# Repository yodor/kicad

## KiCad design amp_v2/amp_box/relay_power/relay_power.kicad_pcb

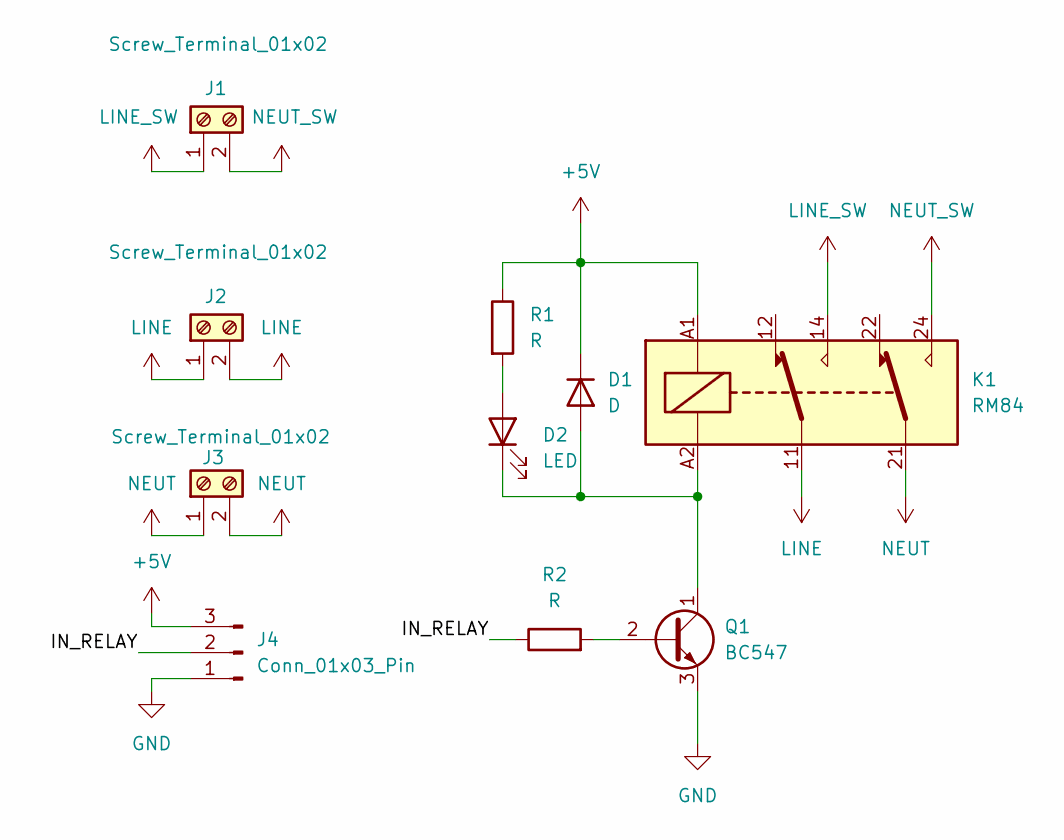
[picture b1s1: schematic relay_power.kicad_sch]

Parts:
D1: D; D_A-405_P7.62mm_Horizontal
D2: LED; LED_Rectangular_W5.0mm_H2.0mm
J1, J2, J3: Screw_Terminal_01x02; TerminalBlock_MaiXu_MX126-5.0-02P_1x02_P5.00mm
J4: Conn_01x03_Pin; PinHeader_1x03_P2.54mm_Vertical
K1: RM84; Relay_DPDT_Finder_40.52
Q1: BC547; TO-92_Inline_Wide
R1, R2: R; R_Axial_DIN0207_L6.3mm_D2.5mm_P10.16mm_Horizontal

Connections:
+5V: D1.1 (K), J4.3, K1.A1, R1.1
/IN_RELAY: J4.2, R2.1
GND: J4.1, Q1.3 (E)
LINE: J2.1, J2.2, K1.11
LINE_SW: J1.1, K1.14
NEUT: J3.1, J3.2, K1.21
NEUT_SW: J1.2, K1.24
unnamed: D1.2 (A), D2.1 (K), K1.A2, Q1.1 (C)
unnamed: D2.2 (A), R1.2
unnamed: Q1.2 (B), R2.2

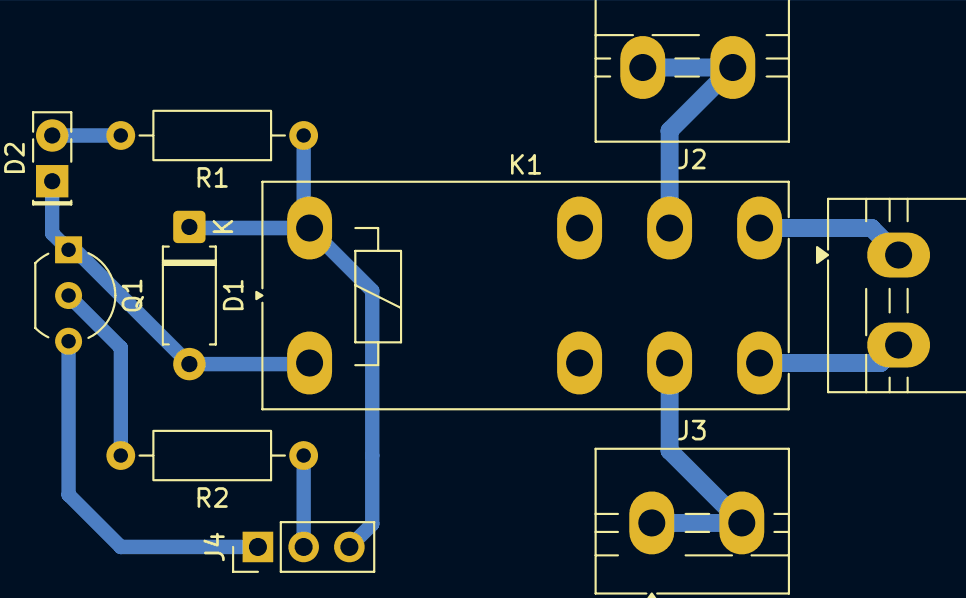
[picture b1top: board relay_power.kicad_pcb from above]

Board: 2 copper layers, 10 parts (0 on the bottom side), 10 nets.

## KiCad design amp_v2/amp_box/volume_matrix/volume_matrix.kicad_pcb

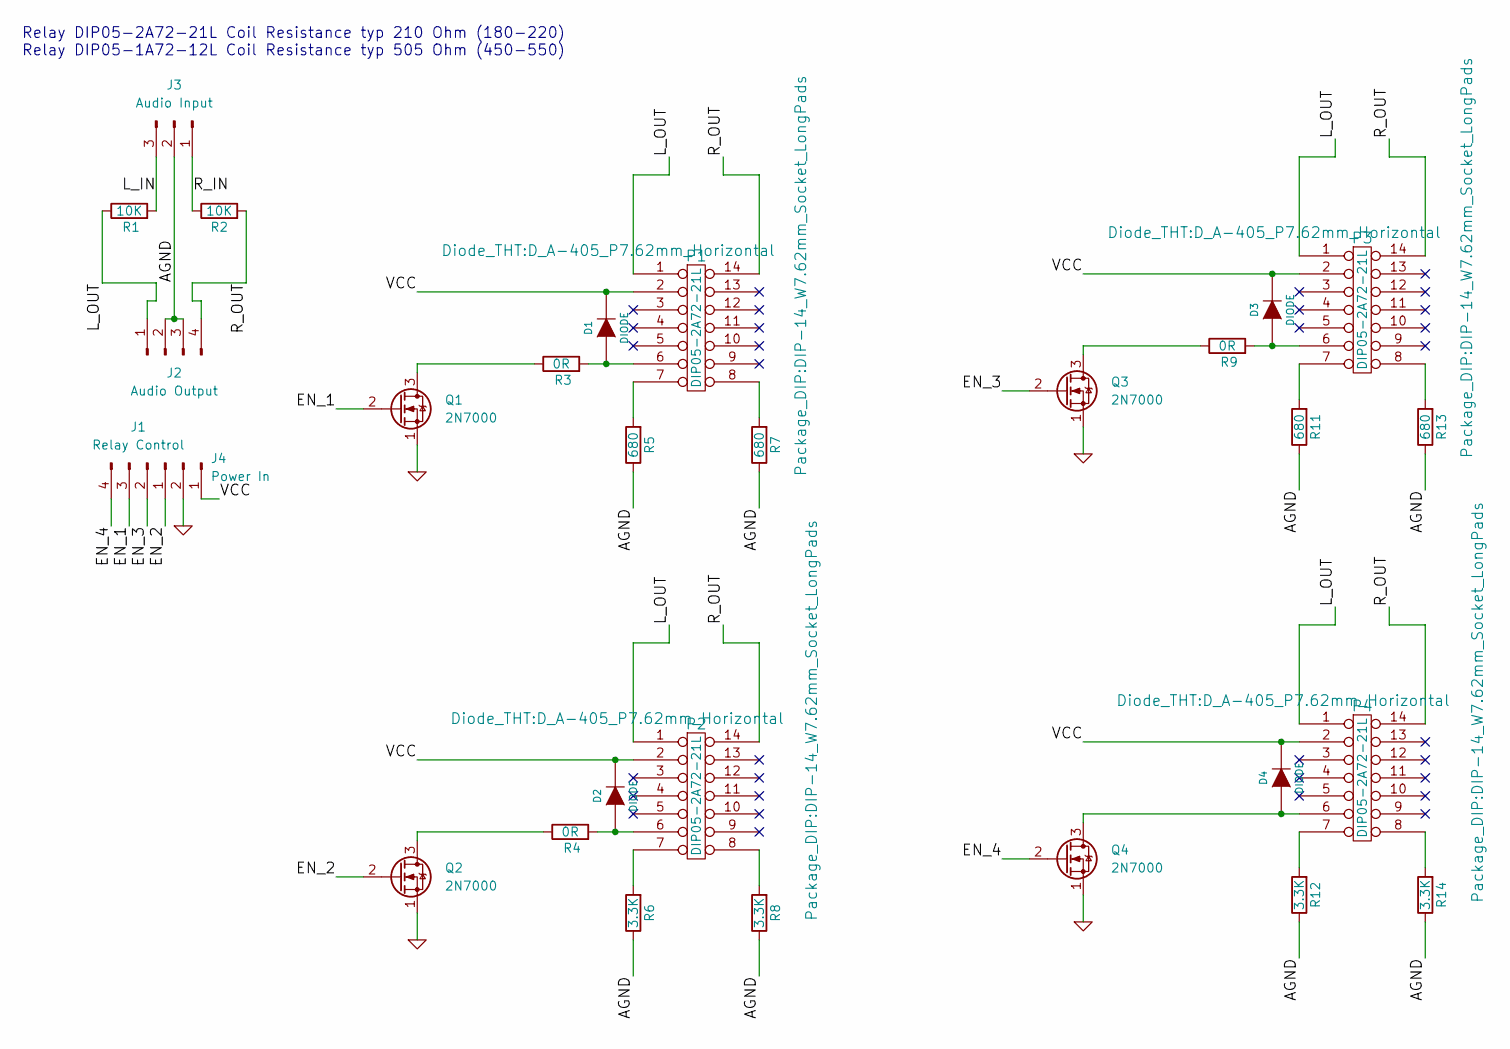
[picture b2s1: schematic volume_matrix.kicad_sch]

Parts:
D1, D2, D3, D4: DIODE; D_A-405_P7.62mm_Horizontal
J1: Relay Control; PinHeader_1x04_P2.54mm_Vertical
J2: Audio Output; JST_XH_B4B-XH-A_1x04_P2.50mm_Vertical
J3: Audio Input; JST_XH_B3B-XH-A_1x03_P2.50mm_Vertical
J4: Power In; PinHeader_1x02_P2.54mm_Vertical
P1, P2, P3, P4: DIP05-2A72-21L; DIP-14_W7.62mm_Socket_LongPads
Q1, Q2, Q3, Q4: 2N7000; TO-92L_Inline_Wide
R1, R2: 10K; R_Axial_DIN0207_L6.3mm_D2.5mm_P7.62mm_Horizontal
R3, R4, R9: 0R; R_Axial_DIN0411_L9.9mm_D3.6mm_P12.70mm_Horizontal
R5, R7, R11, R13: 680; R_Axial_DIN0207_L6.3mm_D2.5mm_P7.62mm_Horizontal
R6, R8, R12, R14: 3.3K; R_Axial_DIN0207_L6.3mm_D2.5mm_P7.62mm_Horizontal

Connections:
/AGND: J2.2, J2.3, J3.2, R5.1, R6.1, R7.1, R8.1, R11.1, R12.1, R13.1, R14.1
/EN_1: J1.3, Q1.2 (G)
/EN_2: J1.1, Q2.2 (G)
/EN_3: J1.2, Q3.2 (G)
/EN_4: J1.4, Q4.2 (G)
/L_IN: J3.3, R1.2
/L_OUT: J2.1, P1.1, P2.1, P3.1, P4.1, R1.1
/R_IN: J3.1, R2.1
/R_OUT: J2.4, P1.14, P2.14, P3.14, P4.14, R2.2
/VCC: D1.2 (K), D2.2 (K), D3.2 (K), D4.2 (K), J4.1, P1.2, P2.2, P3.2, P4.2
GND: J4.2, Q1.1 (S), Q2.1 (S), Q3.1 (S), Q4.1 (S)
unnamed: D1.1 (A), P1.6, R3.2
unnamed: D2.1 (A), P2.6, R4.2
unnamed: D3.1 (A), P3.6, R9.2
unnamed: D4.1 (A), P4.6, Q4.3 (D)
unnamed: P1.7, R5.2
unnamed: P1.8, R7.2
unnamed: P2.7, R6.2
unnamed: P2.8, R8.2
unnamed: P3.7, R11.2
unnamed: P3.8, R13.2
unnamed: P4.7, R12.2
unnamed: P4.8, R14.2
unnamed: Q1.3 (D), R3.1
unnamed: Q2.3 (D), R4.1
unnamed: Q3.3 (D), R9.1

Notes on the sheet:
Relay DIP05-2A72-21L Coil Resistance typ 210 Ohm (180-220) Relay DIP05-1A72-12L Coil Resistance typ 505 Ohm (450-550)

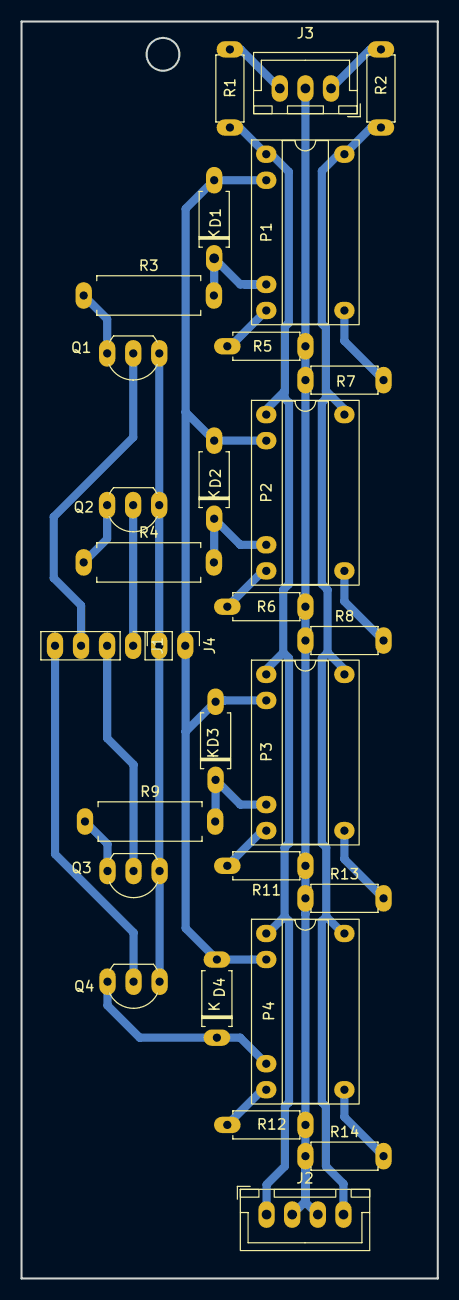
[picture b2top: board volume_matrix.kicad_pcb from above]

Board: 2 copper layers, 40.6 x 122.6 mm, 29 parts (0 on the bottom side), 26 nets.

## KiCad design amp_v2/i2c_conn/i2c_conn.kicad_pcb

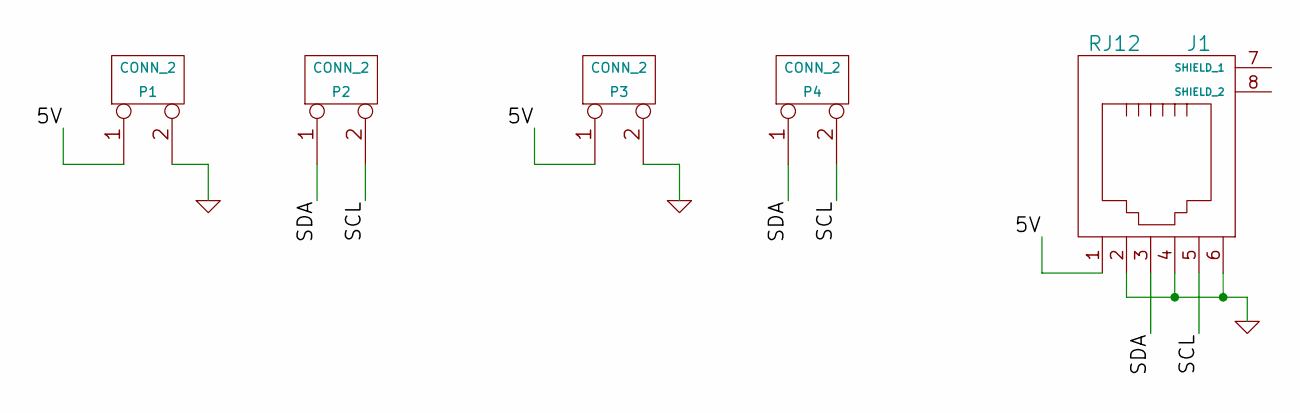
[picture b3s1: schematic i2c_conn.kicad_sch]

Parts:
J1: RJ12
P1, P2, P3, P4: CONN_2

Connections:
/5V: J1.1, P1.1, P3.1
/SCL: J1.5, P2.2 (PM), P4.2 (PM)
/SDA: J1.3, P2.1, P4.1
GND: J1.2, J1.4, J1.6, P1.2 (PM), P3.2 (PM)

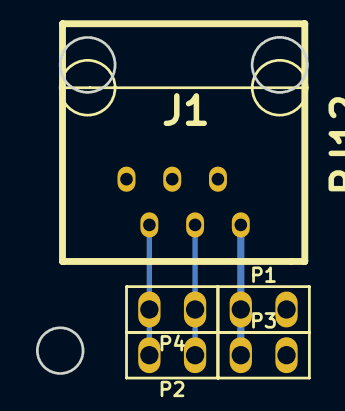
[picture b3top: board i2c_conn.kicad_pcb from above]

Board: 2 copper layers, 15.0 x 18.7 mm, 5 parts (0 on the bottom side), 4 nets.

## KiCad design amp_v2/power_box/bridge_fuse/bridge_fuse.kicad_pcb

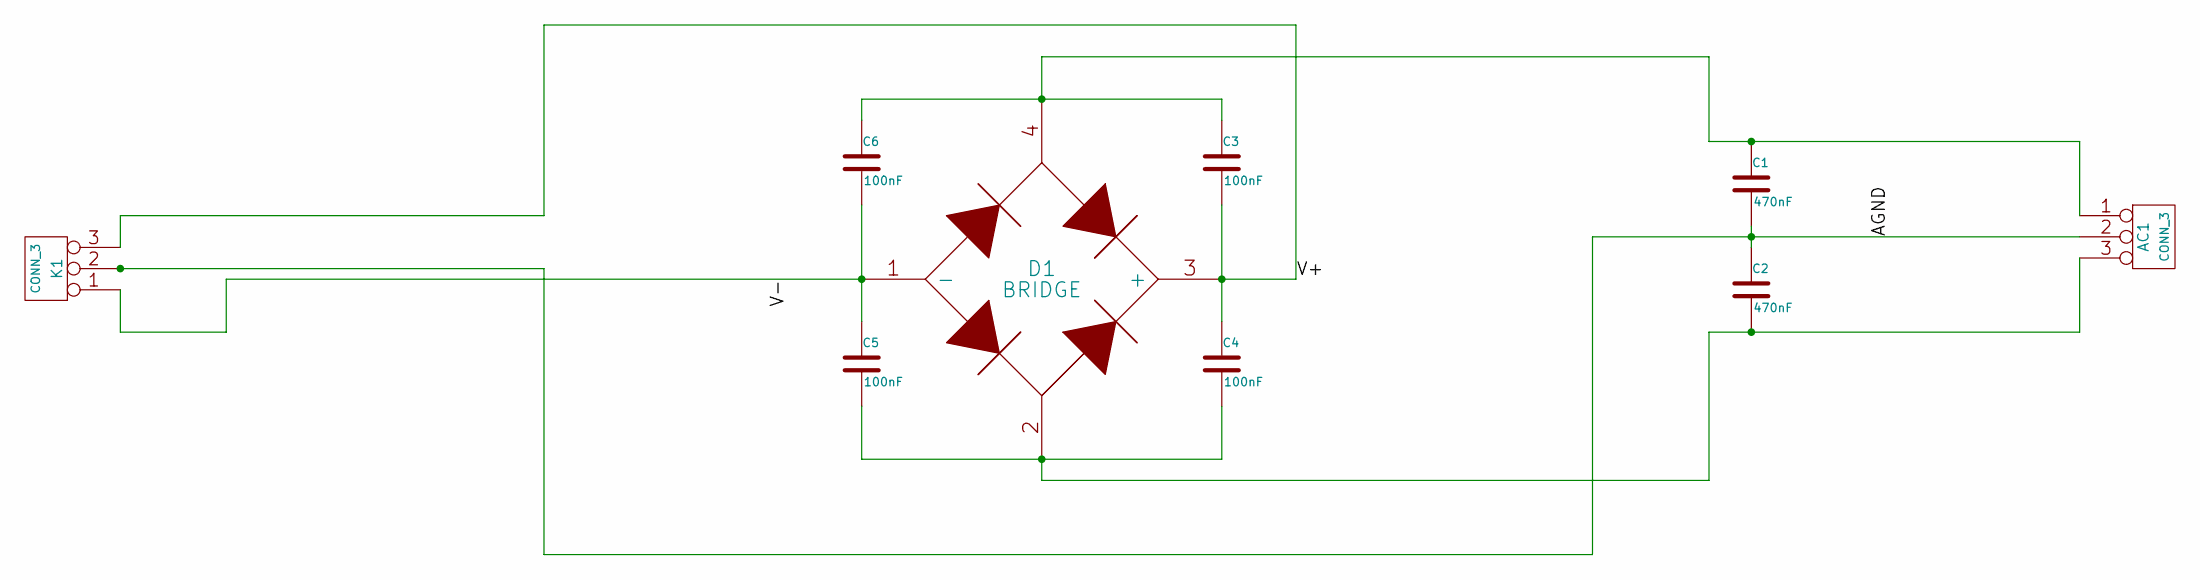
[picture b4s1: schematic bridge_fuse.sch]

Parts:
AC1: CONN_3
C1, C2: 470nF
C3, C4, C5, C6: 100nF
D1: BRIDGE
K1: CONN_3

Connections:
/AGND: AC1.2 (PM), C1.2, C2.1, K1.2 (PM)
/V+: C3.2, C4.1, D1.3 (+), K1.3
/V-: C5.1, C6.2, D1.1 (-), K1.1
unnamed: AC1.3, C2.2, C4.2, C5.2, D1.2
unnamed: AC1.1, C1.1, C3.1, C6.1, D1.4

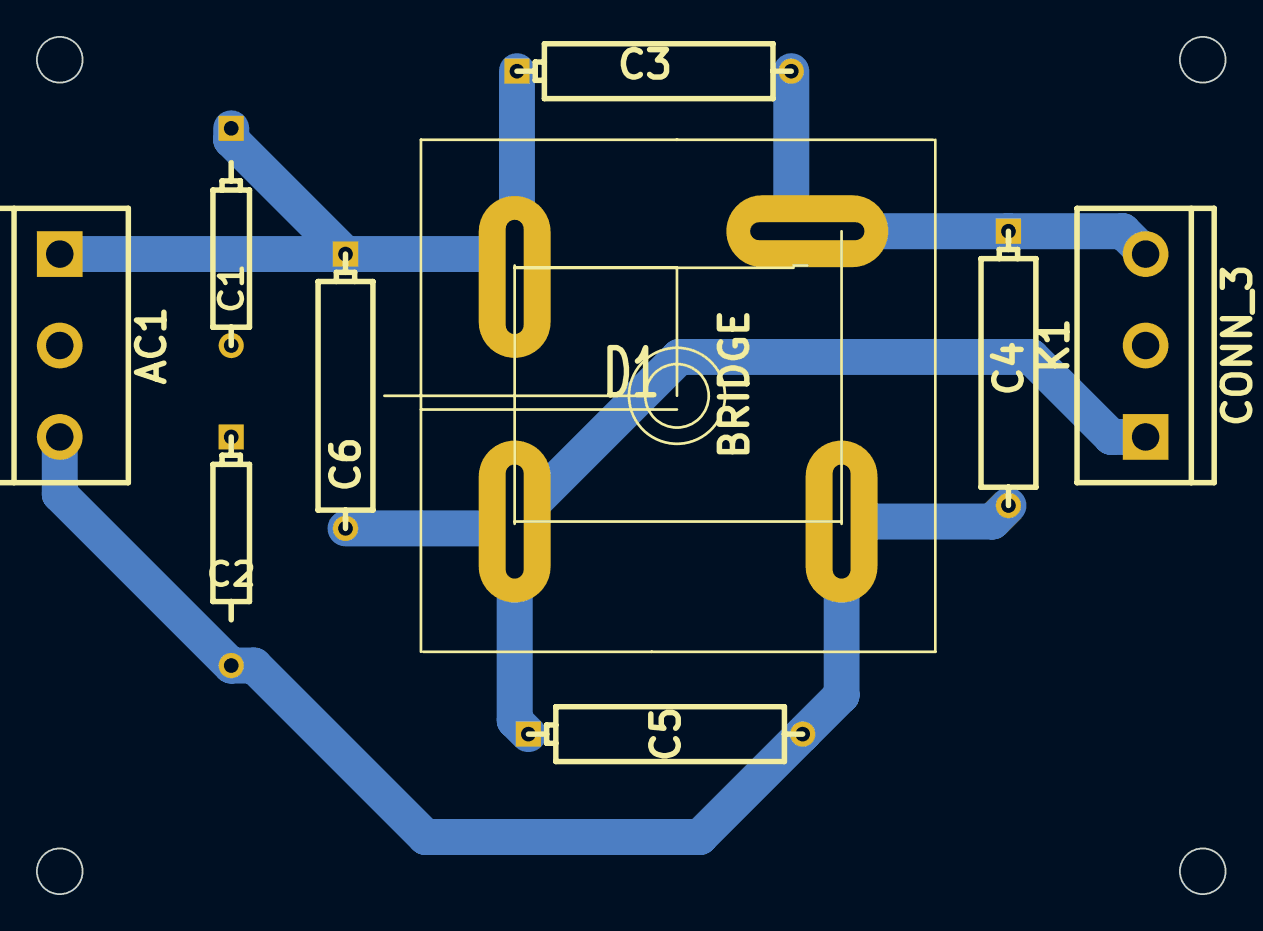
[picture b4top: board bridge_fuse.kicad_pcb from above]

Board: 2 copper layers, 66.0 x 47.6 mm, 9 parts (0 on the bottom side), 5 nets.

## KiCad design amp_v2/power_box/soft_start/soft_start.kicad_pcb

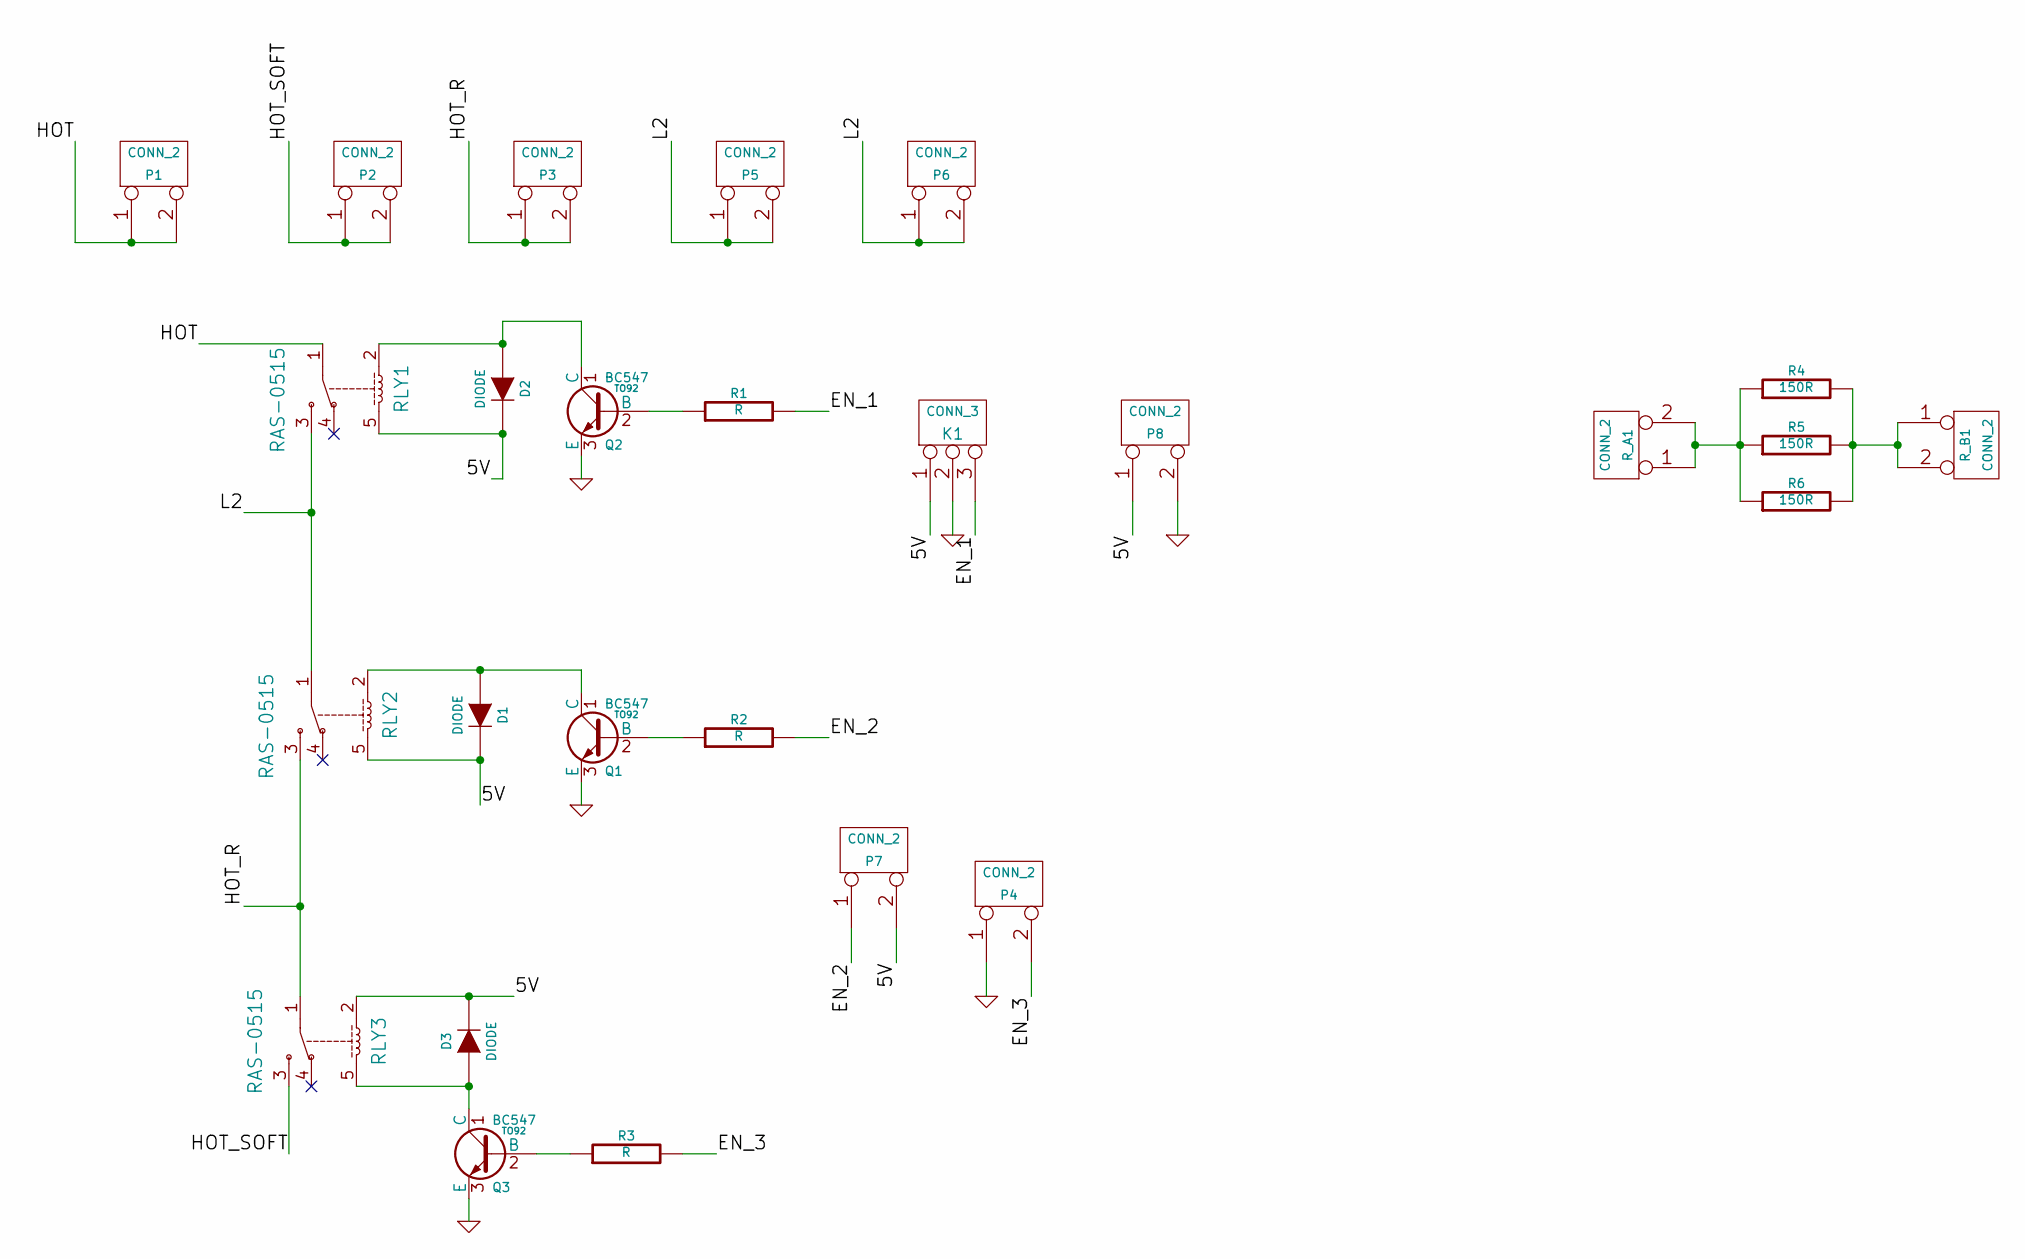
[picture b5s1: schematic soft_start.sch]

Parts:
D1, D2, D3: DIODE
K1: CONN_3
P1, P2, P3, P4, P5, P6, P7, P8: CONN_2
Q1, Q2, Q3: BC547; TO92
R1, R2, R3: R
R4, R5, R6: 150R
RLY1, RLY2, RLY3: RAS-0515
R_A1: CONN_2
R_B1: CONN_2

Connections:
/5V: D1.2 (K), D2.2 (K), D3.2 (K), K1.1, P7.2 (PM), P8.1, RLY1.5, RLY2.5, RLY3.2
/EN_1: K1.3, R1.2
/EN_2: P7.1, R2.2
/EN_3: P4.2 (PM), R3.2
/HOT: P1.1, P1.2 (PM), RLY1.1
/HOT_R: P3.1, P3.2 (PM), RLY2.3, RLY3.1
/HOT_SOFT: P2.1, P2.2 (PM), RLY3.3
/L2: P5.1, P5.2 (PM), P6.1, P6.2 (PM), RLY1.3, RLY2.1
GND: K1.2 (PM), P4.1, P8.2 (PM), Q1.3 (E), Q2.3 (E), Q3.3 (E)
unnamed: Q1.2 (B), R2.1
unnamed: Q3.2 (B), R3.1
unnamed: D2.1 (A), Q2.1 (C), RLY1.2
unnamed: Q2.2 (B), R1.1
unnamed: R4.1, R5.1, R6.1, R_A1.1, R_A1.2 (PM)
unnamed: R4.2, R5.2, R6.2, R_B1.1, R_B1.2 (PM)
unnamed: D1.1 (A), Q1.1 (C), RLY2.2
unnamed: D3.1 (A), Q3.1 (C), RLY3.5

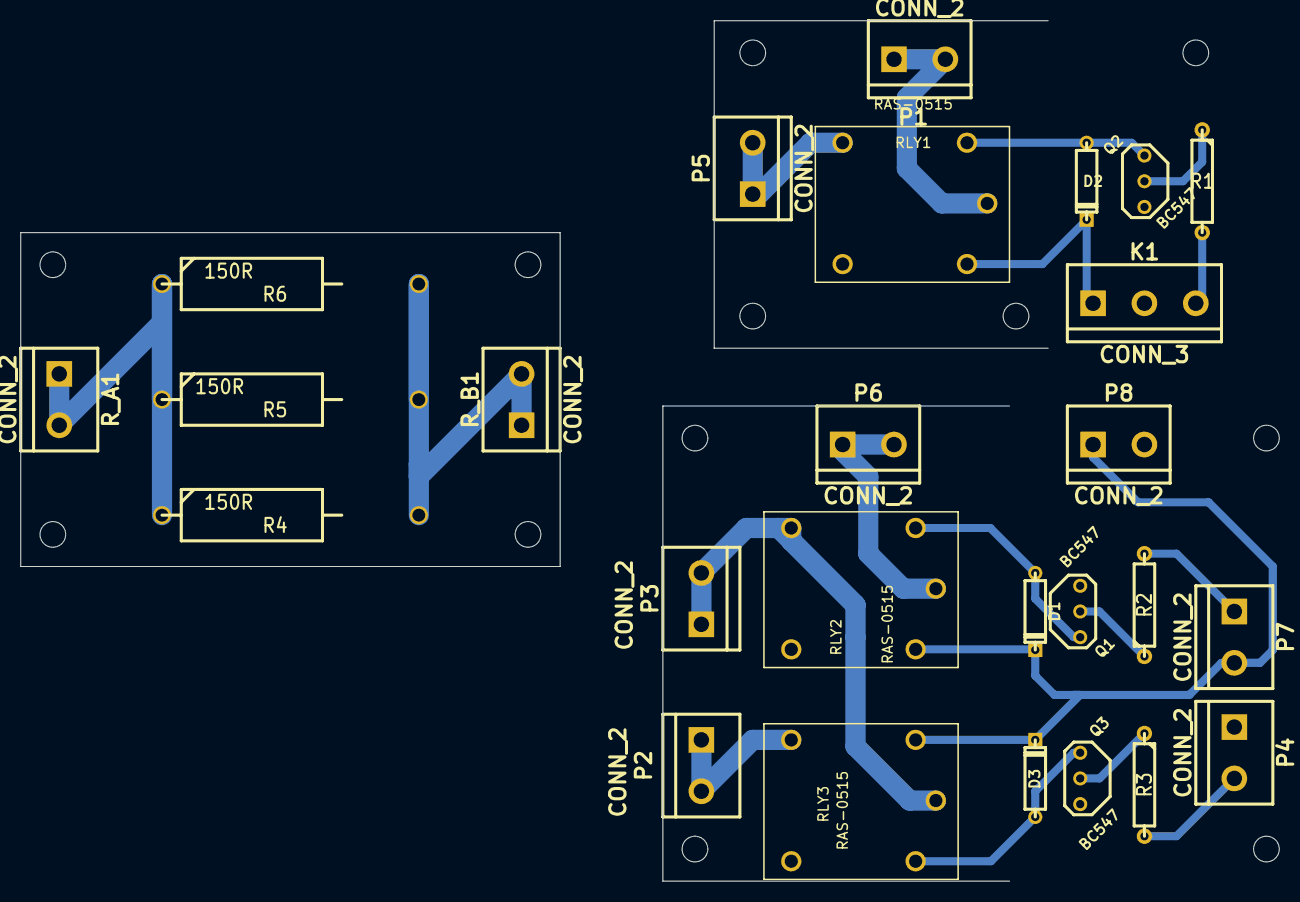
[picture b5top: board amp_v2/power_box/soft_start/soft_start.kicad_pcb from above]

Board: 2 copper layers, 124.5 x 85.1 mm, 26 parts (0 on the bottom side), 17 nets.

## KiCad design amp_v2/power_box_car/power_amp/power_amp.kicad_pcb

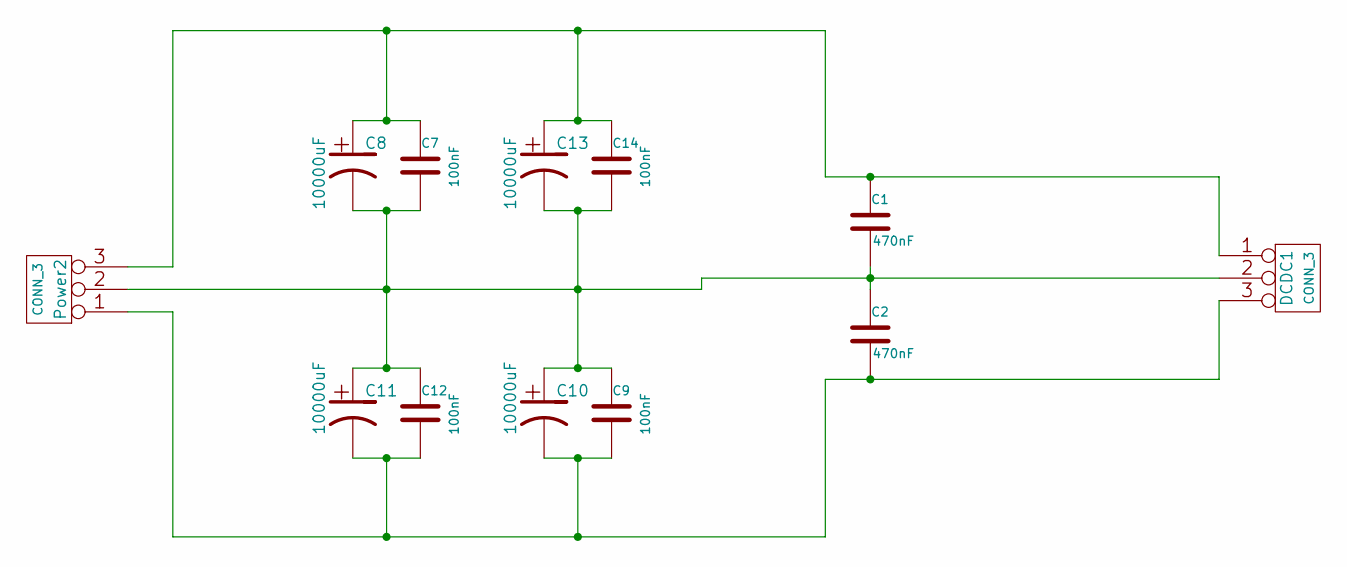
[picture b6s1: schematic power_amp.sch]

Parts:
C1, C2: 470nF
C7, C9, C12, C14: 100nF
C8, C10, C11, C13: 10000uF
DCDC1: CONN_3
Power2: CONN_3

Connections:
unnamed: C2.2, C9.2, C10.2, C11.2, C12.2, DCDC1.3, Power2.1
unnamed: C1.1, C7.1, C8.1, C13.1, C14.1, DCDC1.1, Power2.3
unnamed: C1.2, C2.1, C7.2, C8.2, C9.1, C10.1, C11.1, C12.1, C13.2, C14.2, DCDC1.2 (PM), Power2.2 (PM)

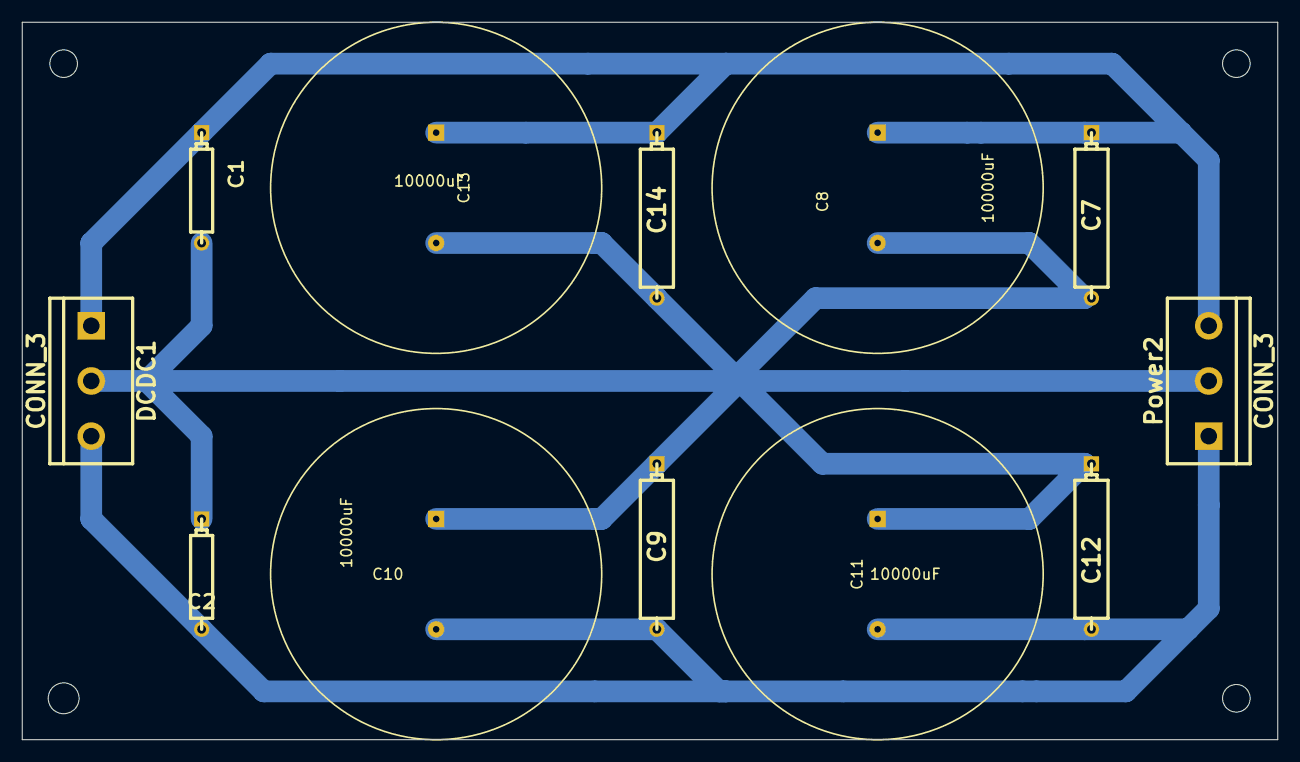
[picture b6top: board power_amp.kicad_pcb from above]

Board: 2 copper layers, 115.6 x 66.0 mm, 12 parts (0 on the bottom side), 3 nets.

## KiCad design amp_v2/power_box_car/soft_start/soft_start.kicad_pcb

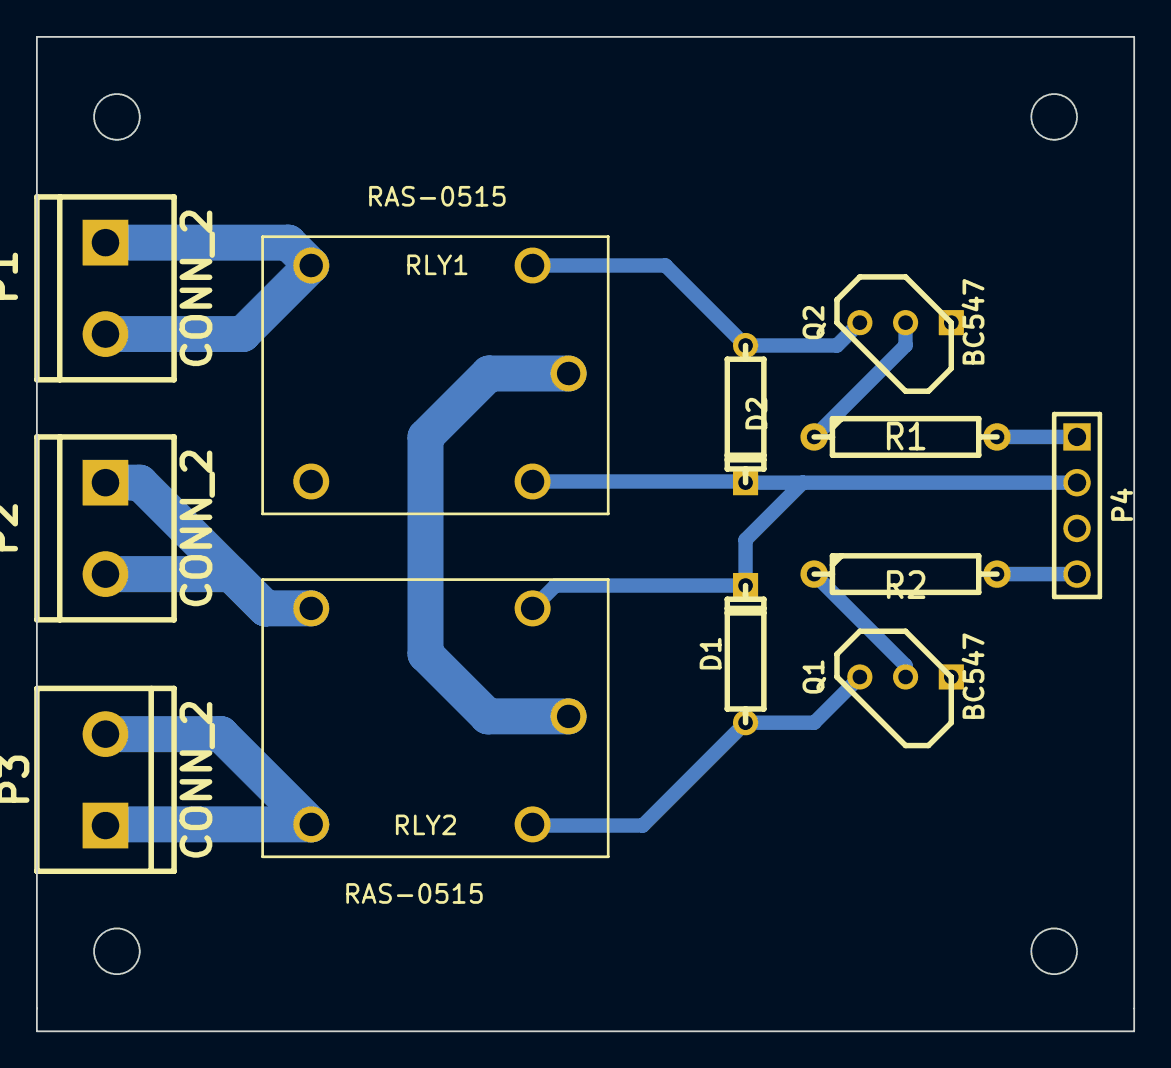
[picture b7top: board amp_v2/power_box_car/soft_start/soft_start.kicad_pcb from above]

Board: 2 copper layers, 61.0 x 55.2 mm, 12 parts (0 on the bottom side), 12 nets.

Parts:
D1, D2: DIODE; D3
P1, P2, P3: CONN_2; bornier2
P4: CONN_4; PIN_ARRAY_4x1
Q1, Q2: BC547; TO92-123
R1, R2: R; R4
RLY1, RLY2: RAS-0515

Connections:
/5V: D1.2, D2.2, P4.2, RLY1.5, RLY2.2
/EN_1: P4.1, R1.2
/EN_2: P4.4, R2.2
/HOT: P1.1, P1.2, RLY1.3
/HOT_R: P3.1, P3.2, RLY2.4
/HOT_SOFT: P2.1, P2.2, RLY2.3
GND: P4.3, Q1.3, Q2.3
unnamed: RLY1.1, RLY2.1
unnamed: Q1.2, R2.1
unnamed: D1.1, Q1.1, RLY2.5
unnamed: D2.1, Q2.1, RLY1.2
unnamed: Q2.2, R1.1

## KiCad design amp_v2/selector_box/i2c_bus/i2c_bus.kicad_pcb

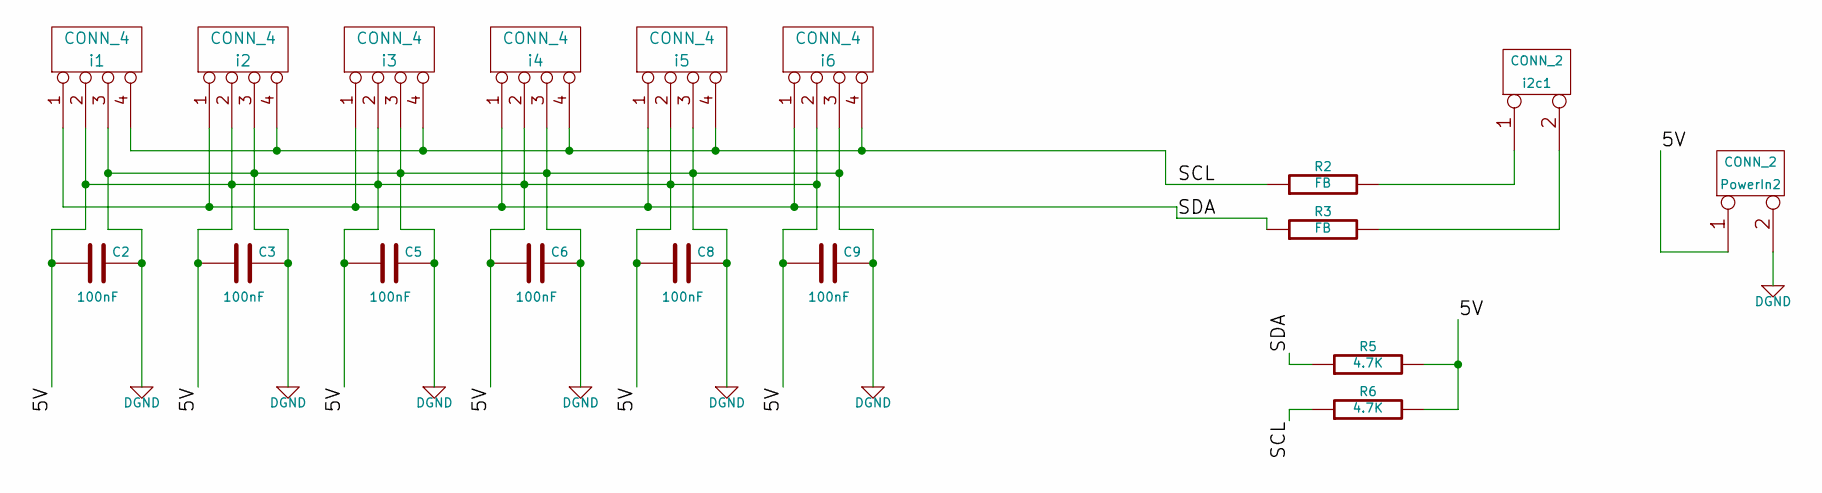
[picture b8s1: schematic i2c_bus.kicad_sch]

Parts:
C2, C3, C5, C6, C8, C9: 100nF
PowerIn2: CONN_2
R2, R3: FB
R5, R6: 4.7K
i1, i2, i3, i4, i5, i6: CONN_4
i2c1: CONN_2

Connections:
/5V: C2.1, C3.1, C5.1, C6.1, C8.1, C9.1, PowerIn2.1, R5.2, R6.2, i1.2, i2.2, i3.2, i4.2, i5.2, i6.2
/SCL: R2.1, R6.1, i1.4, i2.4, i3.4, i4.4, i5.4, i6.4
/SDA: R3.1, R5.1, i1.1, i2.1, i3.1, i4.1, i5.1, i6.1
DGND: C2.2, C3.2, C5.2, C6.2, C8.2, C9.2, PowerIn2.2 (PM), i1.3, i2.3, i3.3, i4.3, i5.3, i6.3
unnamed: R3.2, i2c1.2 (PM)
unnamed: R2.2, i2c1.1

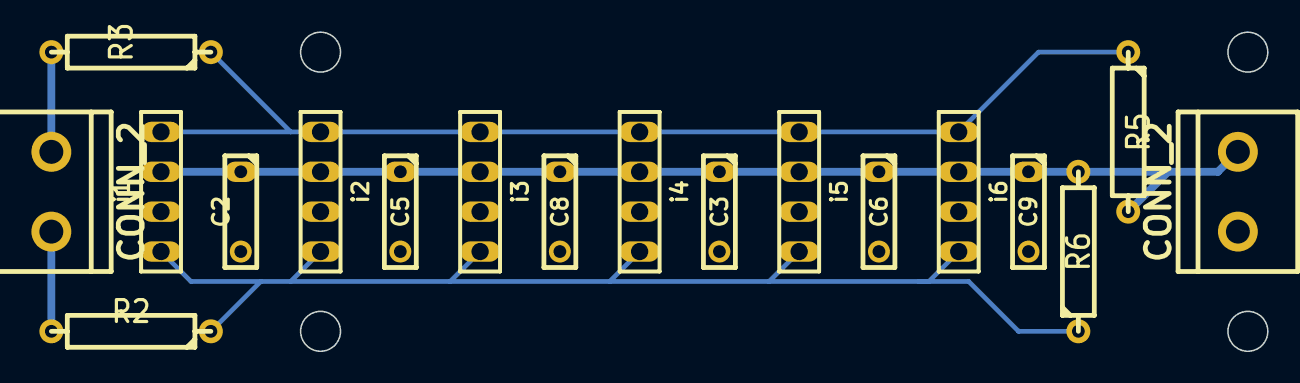
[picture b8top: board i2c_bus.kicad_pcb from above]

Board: 2 copper layers, 18 parts (0 on the bottom side), 6 nets.
